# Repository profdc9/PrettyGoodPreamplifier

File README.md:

# Pretty Good Preamplifier

This is a stereo preamplifier circuit designed by Daniel Marks, including schematic and gerbers.

It has the following features:

1.  Four selectable audio sources, selected by relays.
2.  One of the audio sources is a balanced XLR input, the other three are unbalanced RCA inputs.
3.  Bass and treble tone control (Baxandall tone control).
4.  Balance control.
5.  A subwoofer output with adjustable gain and corner frequency between 20 and 100 Hz.
6.  Unbalanced and balanced (XLR) outputs for stereo and subwoofer channels.
7.  Supports a toggle power switch or a volume knob power switch.
8.  Can be turned on using remote trigger.
0.  Can send a remote trigger signal when turned on (for example to an amplifier).

It is a two-sided PCB that can be manufactured cheaply by, for example, JLCPCB or PCBWay.  The LM4562 is preferentially used for the op-amps, but NE5532 works fine too.  The XLR input uses a THAT1206 or INA137 integrated circuit.  The XLR output uses a THAT1646 or DRV134 integrated circuit.

Here is a picture of the PCB

Here is a picture of the full preamplifier with the potentiometer extenders in the CAD directory:

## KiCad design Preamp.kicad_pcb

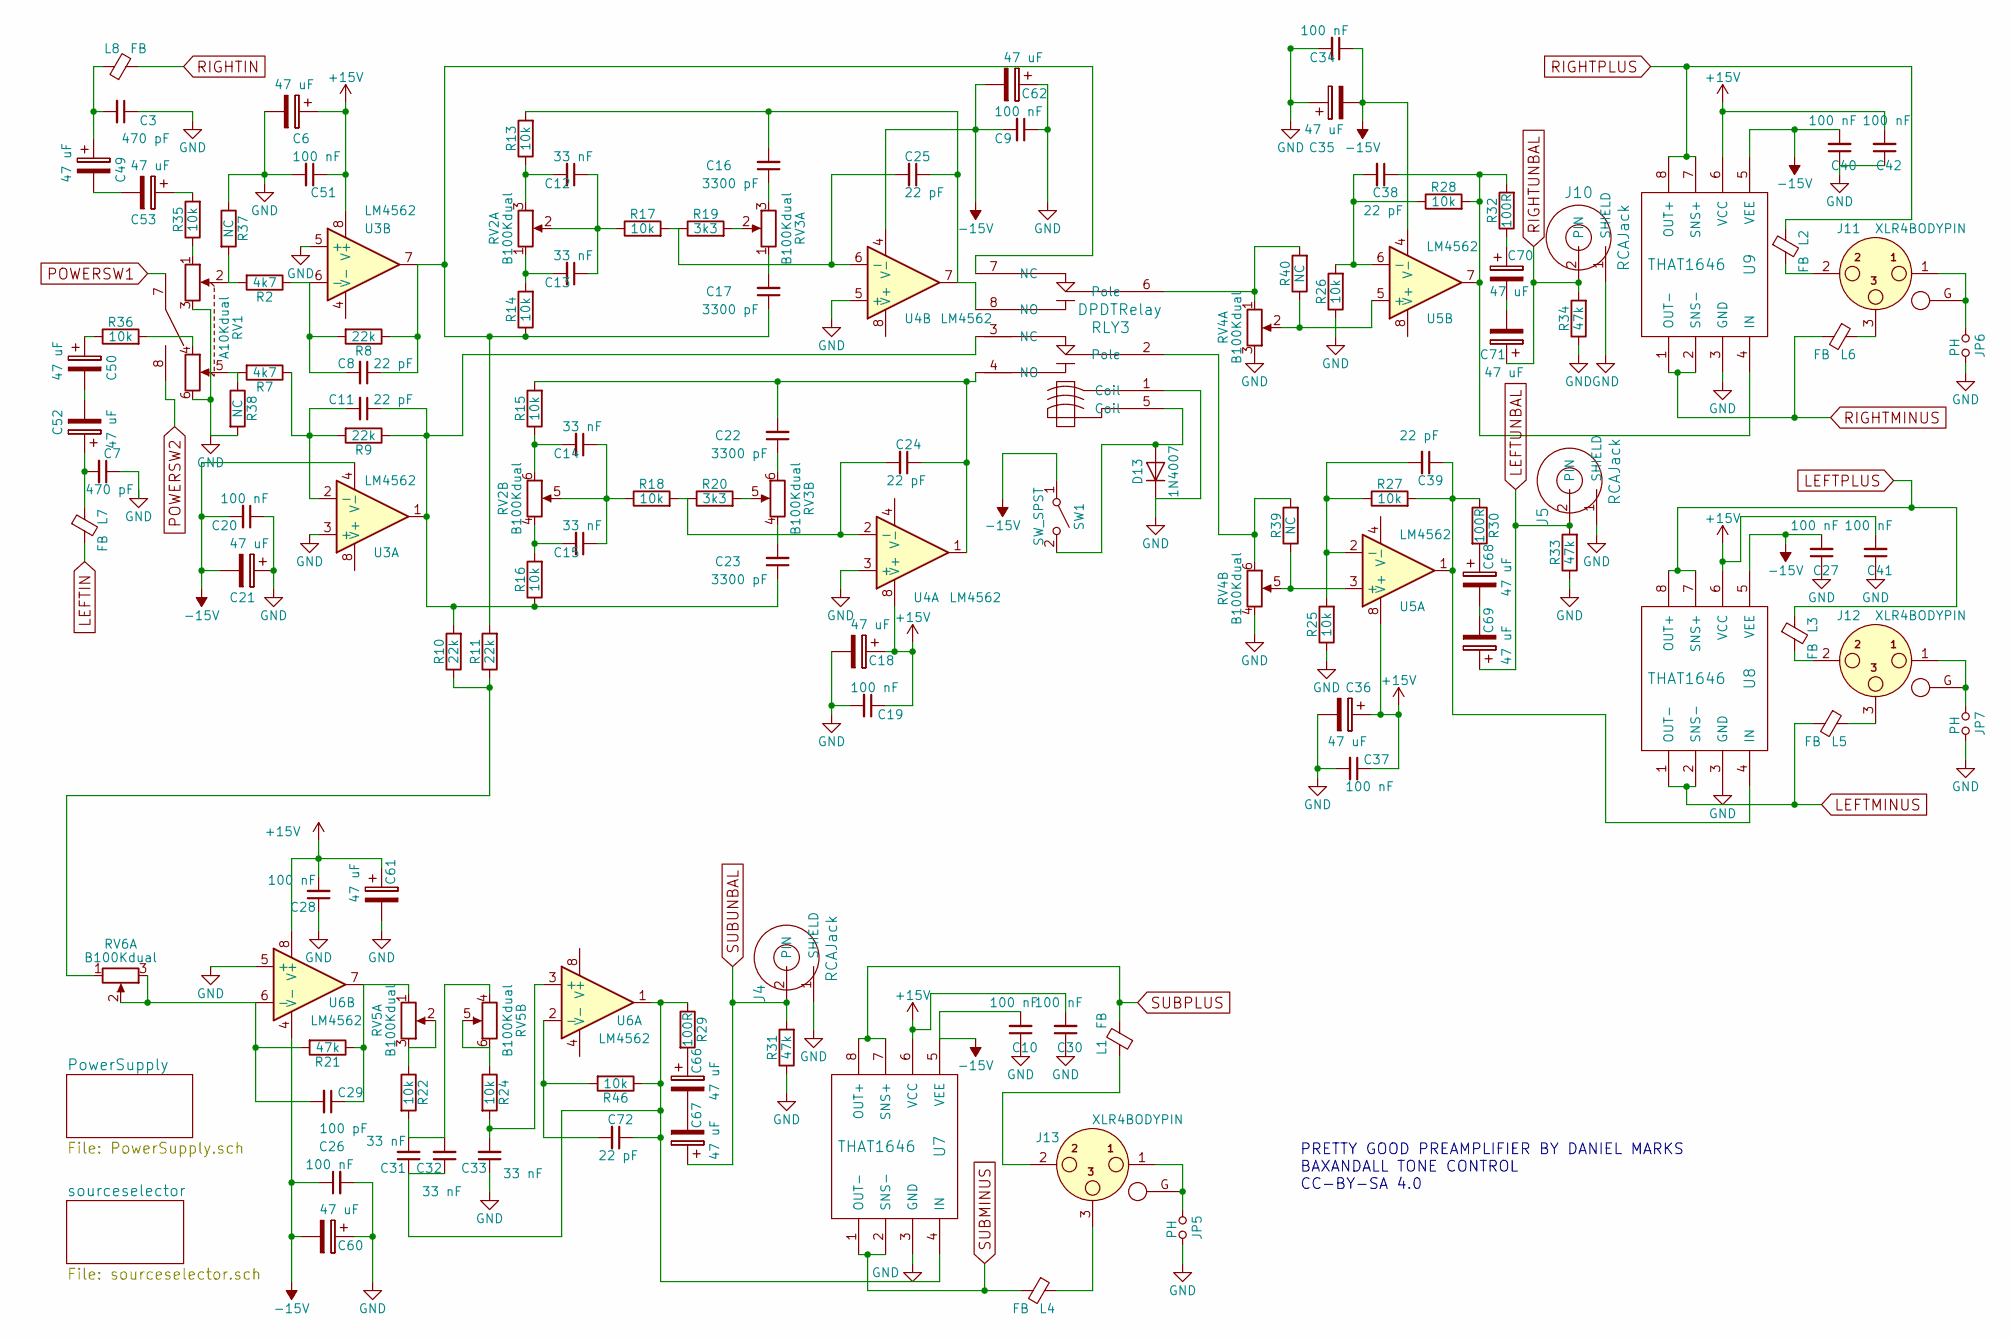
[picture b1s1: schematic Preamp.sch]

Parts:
C3, C7: 470 pF; C_Disc_D5.0mm_W2.5mm_P5.00mm
C6, C18, C21, C35, C36, C49, C50, C52, C53, C60, C61, C62, C66, C67, C68, C69, C70, C71: 47 uF; CP_Radial_D5.0mm_P2.50mm
C8, C11, C24, C25, C38, C39, C72: 22 pF; C_Disc_D5.0mm_W2.5mm_P5.00mm
C9, C10, C19, C20, C26, C27, C28, C30, C34, C37, C40, C41, C42, C51: 100 nF; C_Disc_D5.0mm_W2.5mm_P5.00mm
C12, C13, C14, C15, C31, C32, C33: 33 nF; C_Disc_D5.0mm_W2.5mm_P5.00mm
C16, C17, C22, C23: 3300 pF; C_Disc_D5.0mm_W2.5mm_P5.00mm
C29: 100 pF; C_Disc_D5.0mm_W2.5mm_P5.00mm
D13: 1N4007; D_DO-41_SOD81_P7.62mm_Horizontal
J4, J5, J10: RCAJack; RCAConnectorCommon
J11, J12, J13: XLR4BODYPIN; IOXLR3MEH
JP5, JP6, JP7: PH; Pin_Header_Straight_1x02_Pitch2.54mm
L1, L2, L3, L4, L5, L6, L7, L8: FB; L_Axial_L7.0mm_D3.3mm_P10.16mm_Horizontal_Fastron_MICC
R2, R7: 4k7; R_Axial_DIN0207_L6.3mm_D2.5mm_P7.62mm_Horizontal
R8, R9, R10, R11: 22k; R_Axial_DIN0207_L6.3mm_D2.5mm_P7.62mm_Horizontal
R13, R14, R15, R16, R17, R18, R22, R24, R25, R26, R27, R28, R35, R36, R46: 10k; R_Axial_DIN0207_L6.3mm_D2.5mm_P7.62mm_Horizontal
R19, R20: 3k3; R_Axial_DIN0207_L6.3mm_D2.5mm_P7.62mm_Horizontal
R21, R31, R33, R34: 47k; R_Axial_DIN0207_L6.3mm_D2.5mm_P7.62mm_Horizontal
R29, R30, R32: 100R; R_Axial_DIN0207_L6.3mm_D2.5mm_P7.62mm_Horizontal
R37, R38, R39, R40: NC; R_Axial_DIN0207_L6.3mm_D2.5mm_P7.62mm_Horizontal
RLY3: DPDTRelay; G2VRelay
RV1: A10Kdual; Dual_Potentiometer_Switch_Wide_WirePads
RV2, RV3, RV4, RV5, RV6: B100Kdual; Dual_Potentiometer_Switch_WirePads
SW1: SW_SPST; TerminalBlock_bornier-2_P5.08mm
U3, U4, U5, U6: LM4562; DIP-8_W7.62mm_Socket
U7, U8, U9: THAT1646; DIP-8_W7.62mm_Socket

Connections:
+15V: C6.1, C18.1, C19.1, C28.2, C30.2, C36.1, C37.1, C41.2, C42.2, C51.1, C61.1, U3.8 (V+), U4.8 (V+), U5.8 (V+), U6.8 (V+), U7.6 (VCC), U8.6 (VCC), U9.6 (VCC); also elsewhere on the board
-15V: C9.2, C10.2, C20.2, C21.2, C26.1, C27.2, C34.1, C35.2, C40.2, C60.2, C62.2, SW1.1 (A), U3.4 (V-), U4.4 (V-), U5.4 (V-), U6.4 (V-), U7.5 (VEE), U8.5 (VEE), U9.5 (VEE); also elsewhere on the board
LEFTIN: L7.2; also elsewhere on the board
LEFTMINUS: L5.2, U8.1 (OUT-), U8.2 (SNS-); also elsewhere on the board
LEFTPLUS: L3.1, U8.7 (SNS+), U8.8 (OUT+); also elsewhere on the board
LEFTUNBAL: C69.1, J5.2 (PIN), R33.2; also elsewhere on the board
unnamed: C3.2, C49.1, L8.1
unnamed: C8.2, R2.1, R8.2, U3.6 (-)
unnamed: C11.1, C23.1, R9.1, R10.2, R16.1, RLY3.3 (NC), U3.1
unnamed: C11.2, R7.1, R9.2, U3.2 (-)
unnamed: C12.1, C13.1, R17.1, RV2.2 (5)
unnamed: C12.2, R13.1, RV2.3 (6)
unnamed: C13.2, R14.2, RV2.1 (4)
unnamed: C14.1, C15.1, R18.1, RV2.5
unnamed: C14.2, R15.1, RV2.6
unnamed: C15.2, R16.2, RV2.4
unnamed: C16.1, RV3.3 (6)
unnamed: C16.2, C25.1, R13.2, RLY3.8 (NO), U4.7
unnamed: C8.1, C17.1, R8.1, R11.2, R14.1, RLY3.7 (NC), U3.7
unnamed: C17.2, RV3.1 (4)
unnamed: C22.1, RV3.6
unnamed: C22.2, C24.1, R15.2, RLY3.4 (NO), U4.1
unnamed: C23.2, RV3.4
unnamed: C24.2, R18.2, R20.1, U4.2 (-)
unnamed: C25.2, R17.2, R19.1, U4.6 (-)
unnamed: C29.1, R21.1, RV5.1 (4), U6.7
unnamed: C29.2, R21.2, RV6.2 (5), RV6.3 (6), U6.6 (-)
unnamed: C31.1, C32.1, C72.1, R29.1, R46.1, U6.1, U7.4 (IN)
unnamed: C31.2, C32.2, R22.2, RV5.4
unnamed: C33.2, R24.2, U6.3 (+)
unnamed: C38.1, R28.2, R32.2, U5.7, U9.4 (IN)
unnamed: C38.2, R26.2, R28.1, U5.6 (-)
unnamed: C39.1, R27.2, R30.1, U5.1, U8.4 (IN)
unnamed: C39.2, R25.2, R27.1, U5.2 (-)
unnamed: C49.2, C53.2
unnamed: C50.1, R36.1
unnamed: C50.2, C52.2
unnamed: C7.2, C52.1, L7.1
unnamed: C53.1, R35.2
unnamed: C66.1, R29.2
unnamed: C66.2, C67.2
unnamed: C68.1, R30.2
unnamed: C68.2, C69.2
unnamed: C70.1, R32.1
unnamed: C70.2, C71.2
unnamed: C72.2, R46.2, U6.2 (-)
unnamed: D13.2 (A), RLY3.5 (Coil), SW1.2 (B)
unnamed: J11.1, J11.G, JP6.1
unnamed: J11.2, L2.2
unnamed: J11.3, L6.1
unnamed: J12.1, J12.G, JP7.1
unnamed: J12.2, L3.2
unnamed: J12.3, L5.1
unnamed: J13.1, J13.G, JP5.1
unnamed: J13.2, L1.1
unnamed: J13.3, L4.1
unnamed: R2.2, R37.2, RV1.2
unnamed: R10.1, R11.1, RV6.1 (4)
unnamed: R19.2, RV3.2 (5)
unnamed: R20.2, RV3.5
unnamed: R22.1, RV5.2 (5), RV5.3 (6)
unnamed: R24.1, RV5.5, RV5.6
unnamed: R35.1, RV1.1
unnamed: R36.2, RV1.4
unnamed: R7.2, R38.1, RV1.5
unnamed: R39.1, RV4.5, U5.3 (+)
unnamed: R39.2, RLY3.2 (Pole), RV4.6
unnamed: R40.1, RV4.2 (5), U5.5 (+)
unnamed: R40.2, RLY3.6 (Pole), RV4.1 (4)
POWERSW1: RV1.7 (SW1); also elsewhere on the board
POWERSW2: RV1.8; also elsewhere on the board
RIGHTIN: L8.2; also elsewhere on the board
RIGHTMINUS: L6.2, U9.1 (OUT-), U9.2 (SNS-); also elsewhere on the board
RIGHTPLUS: L2.1, U9.7 (SNS+), U9.8 (OUT+); also elsewhere on the board
RIGHTUNBAL: C71.1, J10.2 (PIN), R34.2; also elsewhere on the board
SUBMINUS: L4.2, U7.1 (OUT-), U7.2 (SNS-); also elsewhere on the board
SUBPLUS: L1.2, U7.7 (SNS+), U7.8 (OUT+); also elsewhere on the board
SUBUNBAL: C67.1, J4.2 (PIN), R31.2; also elsewhere on the board

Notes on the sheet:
PRETTY GOOD PREAMPLIFIER BY DANIEL MARKS BAXANDALL TONE CONTROL CC-BY-SA 4.0

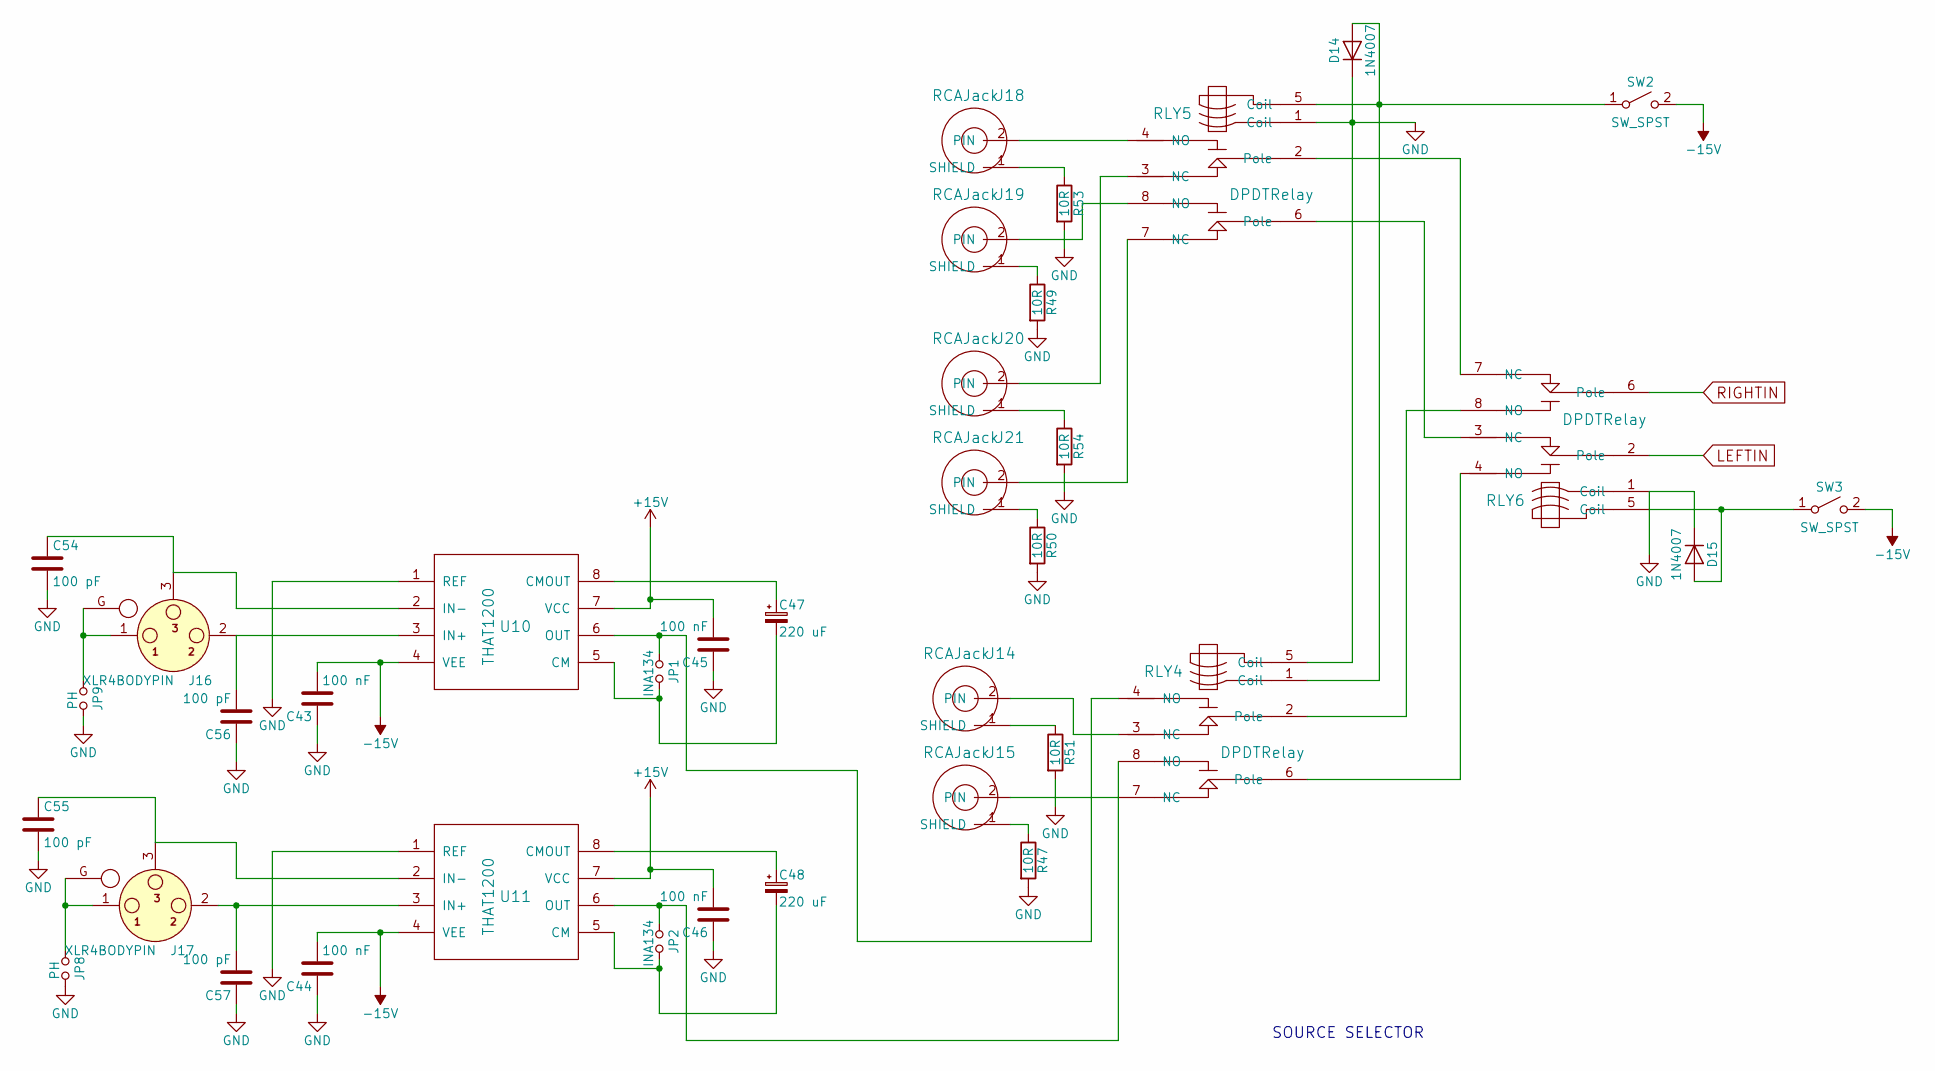
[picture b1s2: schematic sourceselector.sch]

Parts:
C43, C44, C45, C46: 100 nF; C_Disc_D5.0mm_W2.5mm_P5.00mm
C47, C48: 220 uF; CP_Radial_D7.5mm_P2.50mm
C54, C55, C56, C57: 100 pF; C_Disc_D5.0mm_W2.5mm_P5.00mm
D14, D15: 1N4007; D_DO-41_SOD81_P7.62mm_Horizontal
J14, J15, J18, J19, J20, J21: RCAJack; RCAConnectorCommon
J16, J17: XLR4BODYPIN; IOXLR3FEH
JP1, JP2: INA134; Pin_Header_Straight_1x02_Pitch2.54mm
JP8, JP9: PH; Pin_Header_Straight_1x02_Pitch2.54mm
R47, R49, R50, R51, R53, R54: 10R; R_Axial_DIN0207_L6.3mm_D2.5mm_P7.62mm_Horizontal
RLY4, RLY5, RLY6: DPDTRelay; G2VRelay
SW2, SW3: SW_SPST; TerminalBlock_bornier-2_P5.08mm
U10, U11: THAT1200; DIP-8_W7.62mm_Socket

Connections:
+15V: C45.2, C46.2, U10.7 (VCC), U11.7 (VCC); also elsewhere on the board
-15V: C43.2, C44.2, SW2.2 (B), SW3.2 (B), U10.4 (VEE), U11.4 (VEE); also elsewhere on the board
LEFTIN: RLY6.2 (Pole); also elsewhere on the board
unnamed: C47.1, U10.8 (CMOUT)
unnamed: C47.2, JP1.2, U10.5 (CM)
unnamed: C48.1, U11.8 (CMOUT)
unnamed: C48.2, JP2.2, U11.5 (CM)
unnamed: C54.1, J16.3, U10.2 (IN-)
unnamed: C55.1, J17.3, U11.2 (IN-)
unnamed: C56.2, J16.2, U10.3 (IN+)
unnamed: C57.2, J17.2, U11.3 (IN+)
unnamed: D14.2 (A), RLY4.1 (Coil), RLY5.5 (Coil), SW2.1 (A)
unnamed: D15.2 (A), RLY6.5 (Coil), SW3.1 (A)
unnamed: J14.1 (SHIELD), R51.1
unnamed: J14.2 (PIN), RLY4.3 (NC)
unnamed: J15.1 (SHIELD), R47.1
unnamed: J15.2 (PIN), RLY4.7 (NC)
unnamed: J16.1, J16.G, JP9.1
unnamed: J17.1, J17.G, JP8.1
unnamed: J18.1 (SHIELD), R53.1
unnamed: J18.2 (PIN), RLY5.4 (NO)
unnamed: J19.1 (SHIELD), R49.1
unnamed: J19.2 (PIN), RLY5.8 (NO)
unnamed: J20.1 (SHIELD), R54.1
unnamed: J20.2 (PIN), RLY5.3 (NC)
unnamed: J21.1 (SHIELD), R50.1
unnamed: J21.2 (PIN), RLY5.7 (NC)
unnamed: JP1.1, RLY4.4 (NO), U10.6 (OUT)
unnamed: JP2.1, RLY4.8 (NO), U11.6 (OUT)
unnamed: RLY4.2 (Pole), RLY6.8 (NO)
unnamed: RLY4.6 (Pole), RLY6.4 (NO)
unnamed: RLY5.2 (Pole), RLY6.7 (NC)
unnamed: RLY5.6 (Pole), RLY6.3 (NC)
RIGHTIN: RLY6.6 (Pole); also elsewhere on the board

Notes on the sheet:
SOURCE SELECTOR

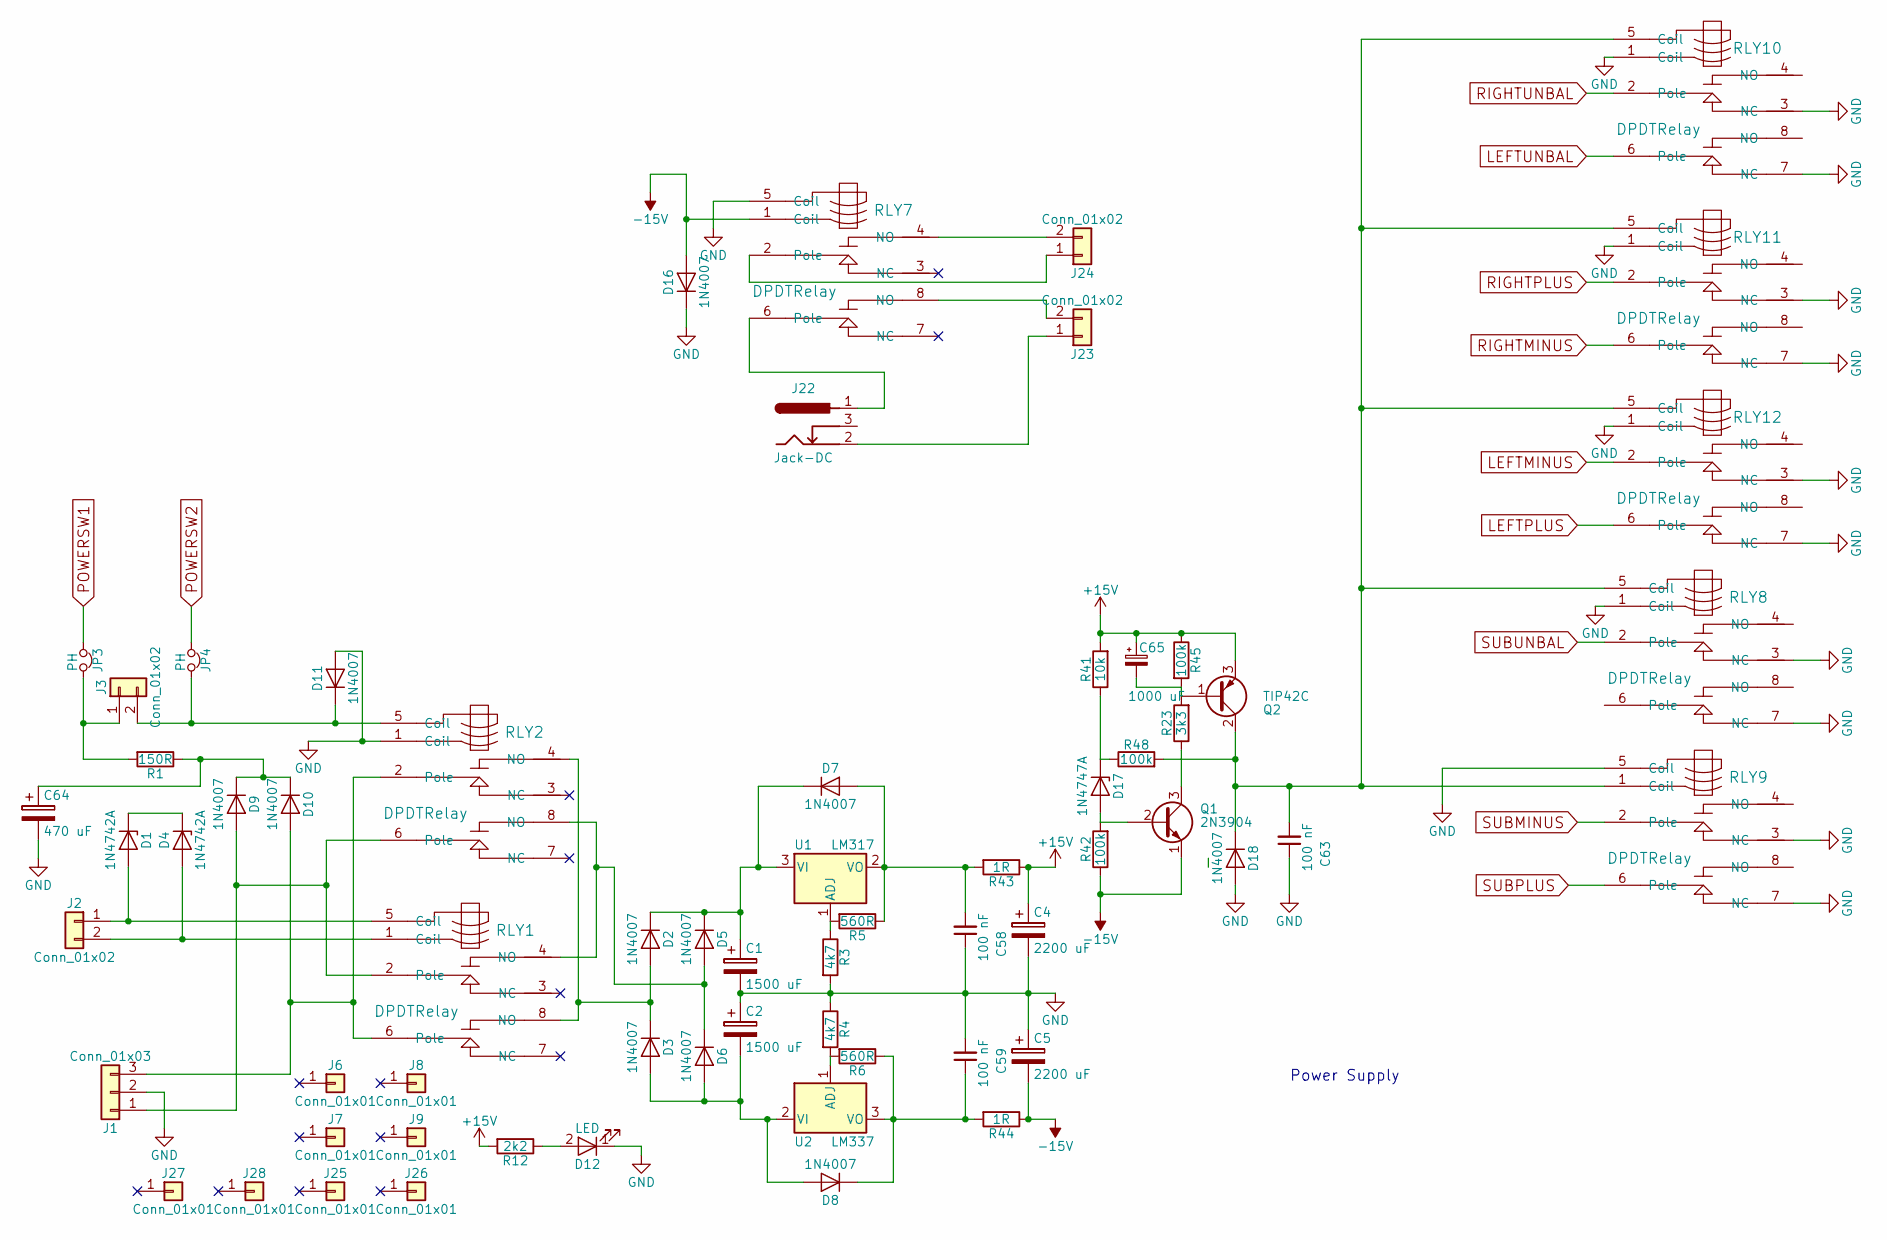
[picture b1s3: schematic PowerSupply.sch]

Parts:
C1, C2: 1500 uF; CP_Radial_D10.0mm_P5.00mm
C4, C5: 2200 uF; CP_Radial_D12.5mm_P5.00mm
C58, C59, C63: 100 nF; C_Disc_D5.0mm_W2.5mm_P5.00mm
C64: 470 uF; CP_Radial_D10.0mm_P5.00mm
C65: 1000 uF; CP_Radial_D7.5mm_P2.50mm
D1, D4: 1N4742A; D_DO-41_SOD81_P7.62mm_Horizontal
D2, D3, D5, D6, D7, D8, D9, D10, D11, D16, D18: 1N4007; D_DO-41_SOD81_P7.62mm_Horizontal
D12: LED; LED_D5.0mm
D17: 1N4747A; D_DO-41_SOD81_P7.62mm_Horizontal
J1: Conn_01x03; TerminalBlock_bornier-3_P5.08mm
J2, J3, J23, J24: Conn_01x02; TerminalBlock_bornier-2_P5.08mm
J6, J7, J8, J9, J25, J26, J27, J28: Conn_01x01; 1pin
J22: Jack-DC; BARREL_JACK
JP3, JP4: PH; Pin_Header_Straight_1x02_Pitch2.54mm
Q1: 2N3904; TO-92_Inline_Wide
Q2: TIP42C; TO-220-3_Vertical
R1: 150R; R_Axial_DIN0309_L9.0mm_D3.2mm_P12.70mm_Horizontal
R3, R4: 4k7; R_Axial_DIN0207_L6.3mm_D2.5mm_P7.62mm_Horizontal
R5, R6: 560R; R_Axial_DIN0207_L6.3mm_D2.5mm_P7.62mm_Horizontal
R12: 2k2; R_Axial_DIN0207_L6.3mm_D2.5mm_P7.62mm_Horizontal
R23: 3k3; R_Axial_DIN0207_L6.3mm_D2.5mm_P7.62mm_Horizontal
R41: 10k; R_Axial_DIN0207_L6.3mm_D2.5mm_P7.62mm_Horizontal
R42, R45, R48: 100k; R_Axial_DIN0207_L6.3mm_D2.5mm_P7.62mm_Horizontal
R43, R44: 1R; R_Axial_DIN0309_L9.0mm_D3.2mm_P12.70mm_Horizontal
RLY1, RLY2, RLY7, RLY8, RLY9, RLY10, RLY11, RLY12: DPDTRelay; G2VRelay
U1: LM317; TO-220-3_Vertical
U2: LM337; TO-220-3_Vertical

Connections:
+15V: C4.1, C65.1, Q2.3 (E), R12.2, R41.2, R43.1, R45.1; also elsewhere on the board
-15V: C5.2, D16.2 (A), Q1.1 (E), R42.1, R44.1, RLY7.1 (Coil); also elsewhere on the board
LEFTMINUS: RLY12.2 (Pole); also elsewhere on the board
LEFTPLUS: RLY12.6 (Pole); also elsewhere on the board
LEFTUNBAL: RLY10.6 (Pole); also elsewhere on the board
unnamed: C1.1, D2.1 (K), D5.1 (K), D7.1 (K), U1.3 (VI)
unnamed: C2.2, D3.2 (A), D6.2 (A), D8.2 (A), U2.2 (VI)
unnamed: C58.2, D7.2 (A), R5.1, R43.2, U1.2 (VO)
unnamed: C59.1, D8.1 (K), R6.1, R44.2, U2.3 (VO)
unnamed: C63.2, D18.1 (K), Q2.2 (C), R48.2, RLY8.5 (Coil), RLY9.1 (Coil), RLY10.5 (Coil), RLY11.5 (Coil), RLY12.5 (Coil)
unnamed: C64.1, D9.1 (K), D10.1 (K), R1.1
unnamed: C65.2, Q2.1 (B), R23.2, R45.2
unnamed: D1.1 (K), D4.1 (K)
unnamed: D1.2 (A), J2.1, RLY1.5 (Coil)
unnamed: D2.2 (A), D3.1 (K), RLY1.8 (NO), RLY2.4 (NO)
unnamed: D4.2 (A), J2.2, RLY1.1 (Coil)
unnamed: D5.2 (A), D6.1 (K), RLY1.4 (NO), RLY2.8 (NO)
unnamed: D9.2 (A), J1.1, RLY1.2 (Pole), RLY2.6 (Pole)
unnamed: D10.2 (A), J1.3, RLY1.6 (Pole), RLY2.2 (Pole)
unnamed: D11.1 (K), J3.2, JP4.2, RLY2.5 (Coil)
unnamed: D12.2 (A), R12.1
unnamed: D17.1 (K), R41.1, R48.1
unnamed: D17.2 (A), Q1.2 (B), R42.2
unnamed: J3.1, JP3.2, R1.2
unnamed: J22.1, RLY7.6 (Pole)
unnamed: J22.2, J23.1
unnamed: J23.2, RLY7.8 (NO)
unnamed: J24.1, RLY7.2 (Pole)
unnamed: J24.2, RLY7.4 (NO)
unnamed: Q1.3 (C), R23.1
unnamed: R3.1, R5.2, U1.1 (ADJ)
unnamed: R4.2, R6.2, U2.1 (ADJ)
POWERSW1: JP3.1; also elsewhere on the board
POWERSW2: JP4.1; also elsewhere on the board
RIGHTMINUS: RLY11.6 (Pole); also elsewhere on the board
RIGHTPLUS: RLY11.2 (Pole); also elsewhere on the board
RIGHTUNBAL: RLY10.2 (Pole); also elsewhere on the board
SUBMINUS: RLY9.2 (Pole); also elsewhere on the board
SUBPLUS: RLY9.6 (Pole); also elsewhere on the board
SUBUNBAL: RLY8.2 (Pole); also elsewhere on the board

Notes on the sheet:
Power Supply

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
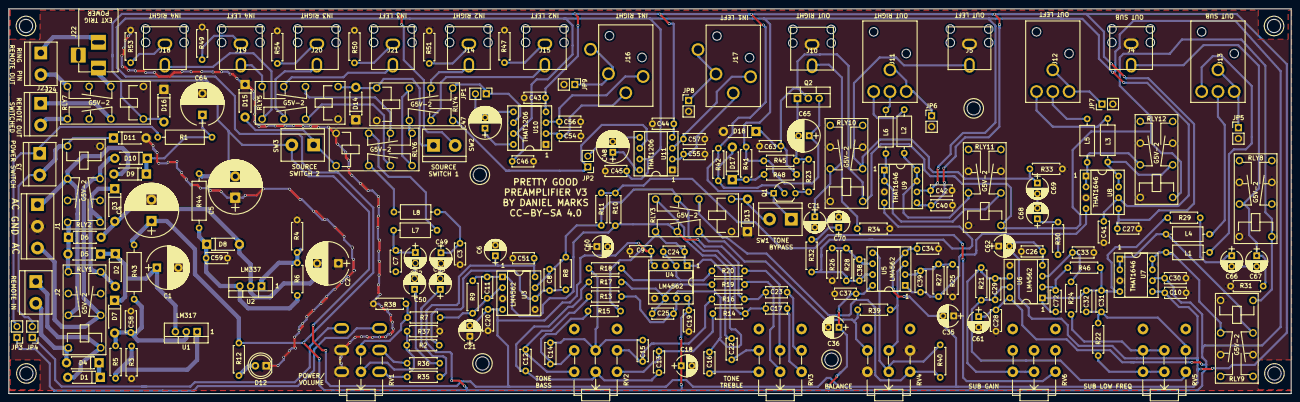
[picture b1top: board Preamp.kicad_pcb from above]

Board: 2 copper layers, 300.0 x 90.0 mm, 222 parts (0 on the bottom side), 136 nets.

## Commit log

2021-03-17 wrote README.md
2021-03-17 wrong again
2021-03-17 Before changing to THAT1646
2021-03-18 Changed balanced output to THAT1646
2021-03-18 Changed one input to be balanced
2021-03-19 Before changing RCA jacks
2021-03-26 JLCPCB 2021-03-26
2021-04-02 Pre off relay
2021-04-02 Tried a relay version out
2021-04-02 Put larger capacitors on
2021-04-06 remove screwy UVLO
2021-04-07 Now grounds all of the outputs when supply is below 20 V
2021-04-13 JLCPCB order 2021-04-11
2021-04-29 Moved around a component to make a little more space
2021-05-04 Added jumpers to connect shields of XLR to ground
2021-05-28 JLCPCB manufacturing
2021-06-28 A few minor changes to fix crowding of components
2021-07-13 Added some more CAD files
2021-07-13 Mistake in extension
